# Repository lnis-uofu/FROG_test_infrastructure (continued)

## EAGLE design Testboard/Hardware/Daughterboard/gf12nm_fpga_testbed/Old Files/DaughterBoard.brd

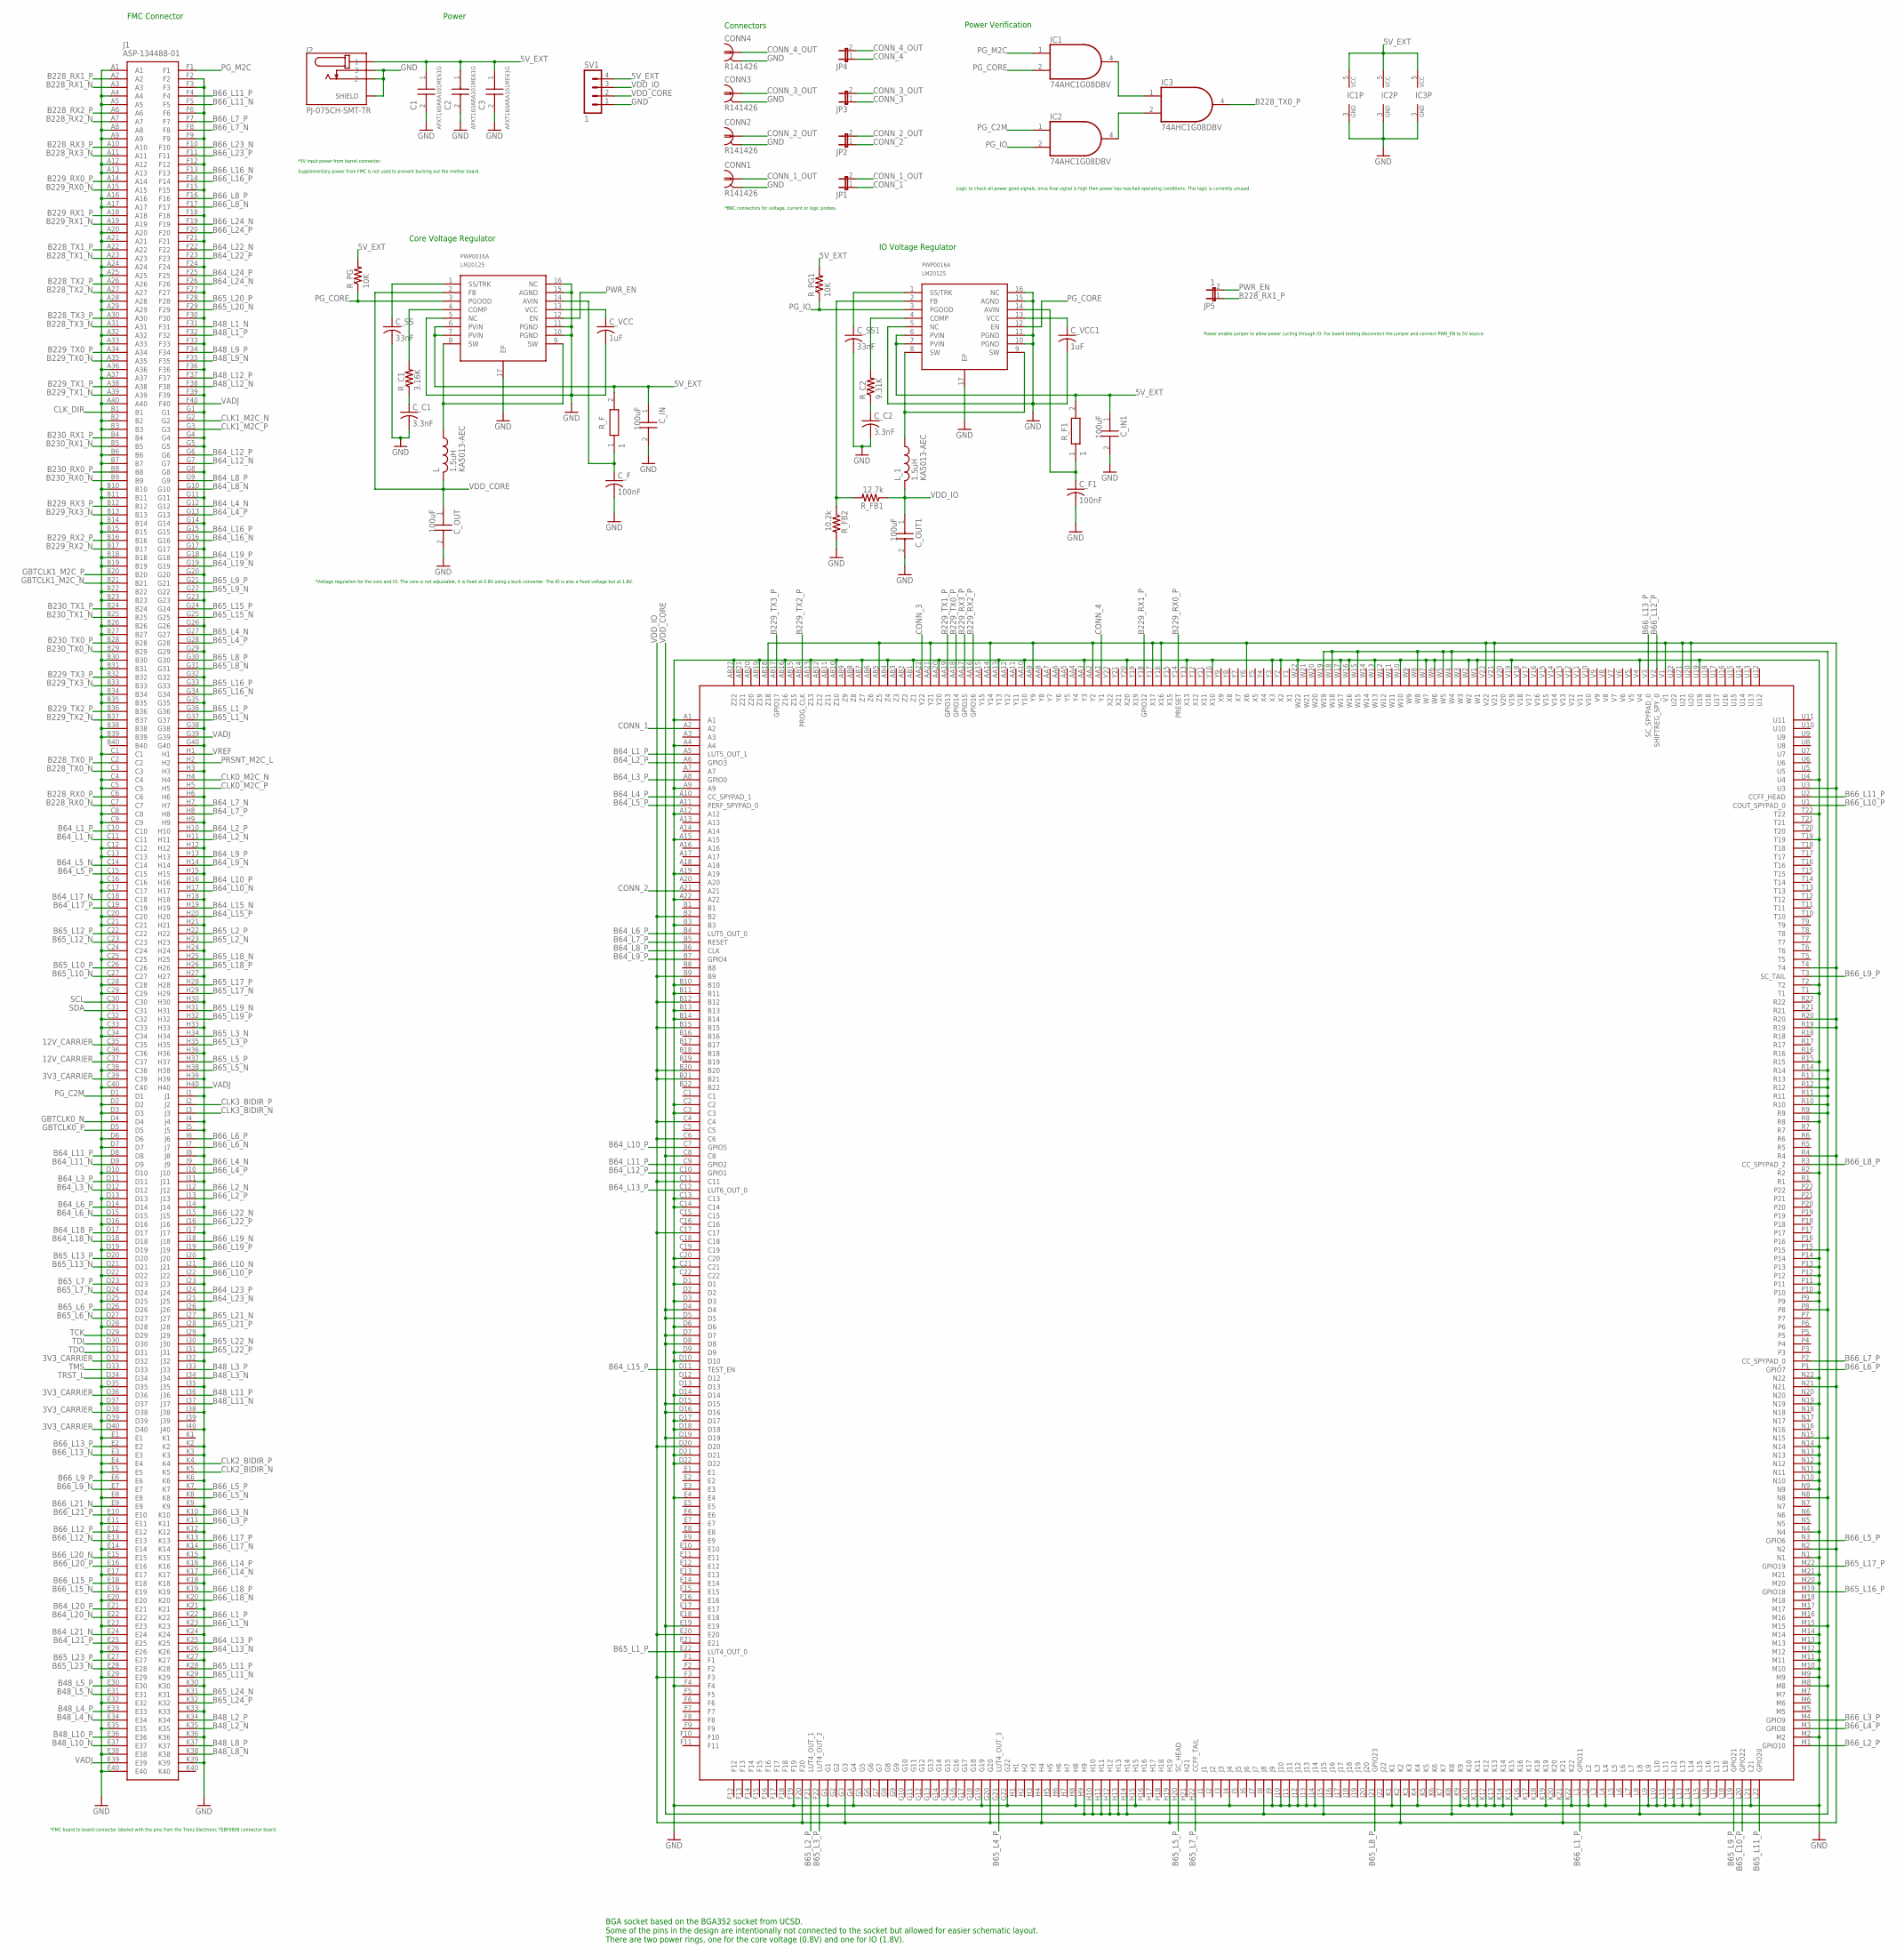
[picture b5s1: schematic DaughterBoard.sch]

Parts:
C1, C2, C3: APXT160ARA101ME61G; CAPAE530X610N
CONN1, CONN2, CONN3, CONN4: R141426
C_C1, C_C2: 3.3nF; C0805
C_F, C_F1: 100nF; C0805
C_IN, C_IN1: 100uF; CAPC2012X145N
C_OUT, C_OUT1: 100uF; CAPC2012X145N
C_SS, C_SS1: 33nF; C0805
C_VCC, C_VCC1: 1uF; C0805
IC1, IC2, IC3: 74AHC1G08DBV; SOT23-5
J1: ASP-134488-01; ASP13448801
J2: PJ-075CH-SMT-TR; CUI_PJ-075CH-SMT-TR
JP1, JP2, JP3, JP4: JP1E; JP1
JP5: 1; JP1
L: KA5013-AEC; INDDFN400X400X180-2N
L_1: KA5013-AEC; INDDFN400X400X180-2N
R_C1: 3.16K; R0805
R_C2: 9.31K; R0805
R_F, R_F1: 1; RESC1608X55N
R_FB1: 12.7k; R0805
R_FB2: 10.2k; R0805
R_PG, R_PG1: 10K; R0805
SV1: 1; MA04-1
U$1, U$3: LM20125/LM20125Q; SOP65P640X120-17T330L
U$2: BGA352; BGA484C100P22X22_2400X2400X220N

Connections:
3V3_CARRIER: J1.C39, J1.D32, J1.D36, J1.D38, J1.D40
5V_EXT: C1.1 (+), C2.1 (+), C3.1 (+), C_IN.1, C_IN1.1, IC1.5 (VCC), IC2.5 (VCC), IC3.5 (VCC), J2.1, R_F.2, R_F1.2, R_PG.2, R_PG1.2, SV1.4, U$1.6 (PVIN), U$1.7 (PVIN), U$3.6 (PVIN), U$3.7 (PVIN)
12V_CARRIER: J1.C35, J1.C37
B48_L1_N: J1.F31
B48_L1_P: J1.F32
B48_L2_N: J1.K35
B48_L2_P: J1.K34
B48_L3_N: J1.J34
B48_L3_P: J1.J33
B48_L4_N: J1.E34
B48_L4_P: J1.E33
B48_L5_N: J1.E31
B48_L5_P: J1.E30
B48_L8_N: J1.K38
B48_L8_P: J1.K37
B48_L9_N: J1.F35
B48_L9_P: J1.F34
B48_L10_N: J1.E37
B48_L10_P: J1.E36
B48_L11_N: J1.J37
B48_L11_P: J1.J36
B48_L12_N: J1.F38
B48_L12_P: J1.F37
B64_L1_N: J1.C11
B64_L1_P: J1.C10, U$2.A5 (LUT5_OUT_1)
B64_L2_N: J1.H11
B64_L2_P: J1.H10, U$2.A6 (GPIO3)
B64_L3_N: J1.D12
B64_L3_P: J1.D11, U$2.A8 (GPIO0)
B64_L4_N: J1.G12
B64_L4_P: J1.G13, U$2.A10 (CC_SPYPAD_1)
B64_L5_N: J1.C14
B64_L5_P: J1.C15, U$2.A11 (PERF_SPYPAD_0)
B64_L6_N: J1.D15
B64_L6_P: J1.D14, U$2.B4 (LUT5_OUT_0)
B64_L7_N: J1.H7
B64_L7_P: J1.H8, U$2.B5 (RESET)
B64_L8_N: J1.G10
B64_L8_P: J1.G9, U$2.B6 (CLK)
B64_L9_N: J1.H14
B64_L9_P: J1.H13, U$2.B7 (GPIO4)
B64_L10_N: J1.H17
B64_L10_P: J1.H16, U$2.C7 (GPIO5)
B64_L11_N: J1.D9
B64_L11_P: J1.D8, U$2.C9 (GPIO2)
B64_L12_N: J1.G7
B64_L12_P: J1.G6, U$2.C10 (GPIO1)
B64_L13_N: J1.K26
B64_L13_P: J1.K25, U$2.C12 (LUT6_OUT_0)
B64_L15_N: J1.H19
B64_L15_P: J1.H20, U$2.D11 (TEST_EN)
B64_L16_N: J1.G16
B64_L16_P: J1.G15
B64_L17_N: J1.C18
B64_L17_P: J1.C19
B64_L18_N: J1.D18
B64_L18_P: J1.D17
B64_L19_N: J1.G19
B64_L19_P: J1.G18
B64_L20_N: J1.E22
B64_L20_P: J1.E21
B64_L21_N: J1.E24
B64_L21_P: J1.E25
B64_L22_N: J1.F22
B64_L22_P: J1.F23
B64_L23_N: J1.J25
B64_L23_P: J1.J24
B64_L24_N: J1.F26
B64_L24_P: J1.F25
B65_L1_N: J1.G37
B65_L1_P: J1.G36, U$2.E22 (LUT4_OUT_0)
B65_L2_N: J1.H23
B65_L2_P: J1.H22, U$2.F21 (LUT4_OUT_1)
B65_L3_N: J1.H34
B65_L3_P: J1.H35, U$2.F22 (LUT4_OUT_2)
B65_L4_N: J1.G27
B65_L4_P: J1.G28, U$2.G21 (LUT4_OUT_3)
B65_L5_N: J1.H38
B65_L5_P: J1.H37, U$2.H20 (SC_HEAD)
B65_L6_N: J1.D27
B65_L6_P: J1.D26
B65_L7_N: J1.D24
B65_L7_P: J1.D23, U$2.H22 (CCFF_TAIL)
B65_L8_N: J1.G31
B65_L8_P: J1.G30, U$2.J21 (GPIO23)
B65_L9_N: J1.G22
B65_L9_P: J1.G21, U$2.L19 (GPIO21)
B65_L10_N: J1.C27
B65_L10_P: J1.C26, U$2.L20 (GPIO22)
B65_L11_N: J1.K29
B65_L11_P: J1.K28, U$2.L22 (GPIO20)
B65_L12_N: J1.C23
B65_L12_P: J1.C22
B65_L13_N: J1.D21
B65_L13_P: J1.D20
B65_L15_N: J1.G25
B65_L15_P: J1.G24
B65_L16_N: J1.G34
B65_L16_P: J1.G33, U$2.M19 (GPIO18)
B65_L17_N: J1.H29
B65_L17_P: J1.H28, U$2.M22 (GPIO19)
B65_L18_N: J1.H25
B65_L18_P: J1.H26
B65_L19_N: J1.H31
B65_L19_P: J1.H32
B65_L20_N: J1.F29
B65_L20_P: J1.F28
B65_L21_N: J1.J27
B65_L21_P: J1.J28
B65_L22_N: J1.J30
B65_L22_P: J1.J31
B65_L23_N: J1.E28
B65_L23_P: J1.E27
B65_L24_N: J1.K31
B65_L24_P: J1.K32
B66_L1_N: J1.K23
B66_L1_P: J1.K22, U$2.L1 (GPIO11)
B66_L2_N: J1.J12
B66_L2_P: J1.J13, U$2.M1 (GPIO10)
B66_L3_N: J1.K10
B66_L3_P: J1.K11, U$2.M4 (GPIO9)
B66_L4_N: J1.J9
B66_L4_P: J1.J10, U$2.M3 (GPIO8)
B66_L5_N: J1.K8
B66_L5_P: J1.K7, U$2.N3 (GPIO6)
B66_L6_N: J1.J7
B66_L6_P: J1.J6, U$2.P1 (GPIO7)
B66_L7_N: J1.F8
B66_L7_P: J1.F7, U$2.P2 (CC_SPYPAD_0)
B66_L8_N: J1.F17
B66_L8_P: J1.F16, U$2.R3 (CC_SPYPAD_2)
B66_L9_N: J1.E7
B66_L9_P: J1.E6, U$2.T3 (SC_TAIL)
B66_L10_N: J1.J21
B66_L10_P: J1.J22, U$2.U1 (COUT_SPYPAD_0)
B66_L11_N: J1.F5
B66_L11_P: J1.F4, U$2.U2 (CCFF_HEAD)
B66_L12_N: J1.E13
B66_L12_P: J1.E12, U$2.V2 (SHIFTREG_SPY_0)
B66_L13_N: J1.E3
B66_L13_P: J1.E2, U$2.V3 (SC_SPYPAD_0)
B66_L14_N: J1.K17
B66_L14_P: J1.K16
B66_L15_N: J1.E19
B66_L15_P: J1.E18
B66_L16_N: J1.F13
B66_L16_P: J1.F14
B66_L17_N: J1.K14
B66_L17_P: J1.K13
B66_L18_N: J1.K20
B66_L18_P: J1.K19
B66_L19_N: J1.J18
B66_L19_P: J1.J19
B66_L20_N: J1.E15
B66_L20_P: J1.E16
B66_L21_N: J1.E9
B66_L21_P: J1.E10
B66_L22_N: J1.J15
B66_L22_P: J1.J16
B66_L23_N: J1.F10
B66_L23_P: J1.F11
B66_L24_N: J1.F19
B66_L24_P: J1.F20
B228_RX0_N: J1.C7
B228_RX0_P: J1.C6
B228_RX1_N: J1.A3
B228_RX1_P: J1.A2, JP5.1
B228_RX2_N: J1.A7
B228_RX2_P: J1.A6
B228_RX3_N: J1.A11
B228_RX3_P: J1.A10
B228_TX0_N: J1.C3
B228_TX0_P: IC3.4 (O), J1.C2
B228_TX1_N: J1.A23
B228_TX1_P: J1.A22
B228_TX2_N: J1.A27
B228_TX2_P: J1.A26
B228_TX3_N: J1.A31
B228_TX3_P: J1.A30
B229_RX0_N: J1.A15
B229_RX0_P: J1.A14, U$2.Y14 (PRESET)
B229_RX1_N: J1.A19
B229_RX1_P: J1.A18, U$2.Y18 (GPIO12)
B229_RX2_N: J1.B17
B229_RX2_P: J1.B16, U$2.AA16 (GPIO16)
B229_RX3_N: J1.B13
B229_RX3_P: J1.B12, U$2.AA17 (GPIO15)
B229_TX0_N: J1.A35
B229_TX0_P: J1.A34, U$2.AA18 (GPIO14)
B229_TX1_N: J1.A39
B229_TX1_P: J1.A38, U$2.AA19 (GPIO13)
B229_TX2_N: J1.B37
B229_TX2_P: J1.B36, U$2.AB14 (PROG_CLK)
B229_TX3_N: J1.B33
B229_TX3_P: J1.B32, U$2.AB17 (GPIO17)
B230_RX0_N: J1.B9
B230_RX0_P: J1.B8
B230_RX1_N: J1.B5
B230_RX1_P: J1.B4
B230_TX0_N: J1.B29
B230_TX0_P: J1.B28
B230_TX1_N: J1.B25
B230_TX1_P: J1.B24
CLK0_M2C_N: J1.H4
CLK0_M2C_P: J1.H5
CLK1_M2C_N: J1.G2
CLK1_M2C_P: J1.G3
CLK2_BIDIR_N: J1.K5
CLK2_BIDIR_P: J1.K4
CLK3_BIDIR_N: J1.J3
CLK3_BIDIR_P: J1.J2
CLK_DIR: J1.B1
CONN_1: JP1.1, U$2.A2
CONN_1_OUT: CONN1.1, JP1.2
CONN_2: JP2.1, U$2.A21
CONN_2_OUT: CONN2.1, JP2.2
CONN_3: JP3.1, U$2.AA22 (Y22)
CONN_3_OUT: CONN3.1, JP3.2
CONN_4: JP4.1, U$2.AA1 (Y1)
CONN_4_OUT: CONN4.1, JP4.2
FB: R_FB1.2, R_FB2.1, U$3.2 (FB)
GBTCLK0_N: J1.D4
GBTCLK0_P: J1.D5
GBTCLK1_M2C_N: J1.B21
GBTCLK1_M2C_P: J1.B20
GND: C1.2 (-), C2.2 (-), C3.2 (-), CONN1.2, CONN1.3 (2), CONN1.4 (2), CONN1.5 (2), CONN2.2, CONN2.3 (2), CONN2.4 (2), CONN2.5 (2), CONN3.2, CONN3.3 (2), CONN3.4 (2), CONN3.5 (2), CONN4.2, CONN4.3 (2), CONN4.4 (2), CONN4.5 (2), C_C1.2, C_C2.2, C_F.2, C_F1.2, C_IN.2, C_IN1.2, C_OUT.2, C_OUT1.2, C_SS.2, C_SS1.2, C_VCC.2, C_VCC1.2, IC1.3 (GND), IC2.3 (GND), IC3.3 (GND), J1.A1, J1.A4, J1.A5, J1.A8, J1.A9, J1.A12, J1.A13, J1.A16, J1.A17, J1.A20, J1.A21, J1.A24, J1.A25, J1.A28, J1.A29, J1.A32, J1.A33, J1.A36, J1.A37, J1.A40, J1.B2, J1.B3, J1.B6, J1.B7, J1.B10, J1.B11, J1.B14, J1.B15, J1.B18, J1.B19, J1.B22, J1.B23, J1.B26, J1.B27, J1.B30, J1.B31, J1.B34, J1.B35, J1.B38, J1.B39, J1.C1, J1.C4, J1.C5, J1.C8, J1.C9, J1.C12, J1.C13, J1.C16, J1.C17, J1.C20, J1.C21, J1.C24, J1.C25, J1.C28, J1.C29, J1.C32, J1.C33, J1.C34, J1.C36, J1.C38, J1.C40, J1.D2, J1.D3, J1.D6, J1.D7, J1.D10, J1.D13, J1.D16, J1.D19, J1.D22, J1.D25, J1.D28, J1.D35, J1.D37, J1.D39, J1.E1, J1.E4, J1.E5, J1.E8, J1.E11, J1.E14, J1.E17, J1.E20, J1.E23, J1.E26, J1.E29, J1.E32, J1.E35, J1.E38, J1.E40, J1.F2, J1.F3, J1.F6, J1.F9, J1.F12, J1.F15, J1.F18, J1.F21, J1.F24, J1.F27, J1.F30, J1.F33, J1.F36, J1.F39, J1.G1, J1.G4, J1.G5, J1.G8, J1.G11, J1.G14, J1.G17, J1.G20, J1.G23, J1.G26, J1.G29, J1.G32, J1.G35, J1.G38, J1.G40, J1.H3, J1.H6, J1.H9, J1.H12, J1.H15, J1.H18, J1.H21, J1.H24, J1.H27, J1.H30, J1.H33, J1.H36, J1.H39, J1.J1, J1.J4, J1.J5, J1.J8, J1.J11, J1.J14, J1.J17, J1.J20, J1.J23, J1.J26, J1.J29, J1.J32, J1.J35, J1.J38, J1.J40, J1.K2, J1.K3, J1.K6, J1.K9, J1.K12, J1.K15, J1.K18, J1.K21, J1.K24, J1.K27, J1.K30, J1.K33, J1.K36, J1.K39, J2.2, J2.3, J2.4 (SHIELD), J2.5 (SHIELD), R_FB2.2, SV1.1, U$1.5 (NC), U$1.10 (PGND), U$1.11 (PGND), U$1.15 (AGND), U$1.16 (NC), U$1.17 (EP), U$2.A1, U$2.A4, U$2.A9, U$2.A12, U$2.A15, U$2.A19, U$2.A22, U$2.AA3 (Y3), U$2.AA10 (Y10), U$2.AA13 (Y13), U$2.AA20 (Y20), U$2.AB1 (Z1), U$2.AB4 (Z4), U$2.AB7 (Z7), U$2.AB10 (Z10), U$2.AB13 (Z13), U$2.AB16 (Z16), U$2.AB19 (Z19), U$2.AB22 (Z22), U$2.B3, U$2.B10, U$2.B11, U$2.B13, U$2.B14, U$2.C2, U$2.C3, U$2.C13, U$2.C14, U$2.C20, U$2.C21, U$2.D1, U$2.D3, U$2.D6, U$2.D9, U$2.D10, U$2.D14, U$2.D17, U$2.D18, U$2.D21, U$2.D22, U$2.E4, U$2.F4, U$2.F19, U$2.G1, U$2.G4, U$2.G19, U$2.G22, U$2.H8, U$2.H15, U$2.J4, U$2.J9, U$2.J10, U$2.J11, U$2.J12, U$2.J13, U$2.J14, U$2.K1, U$2.K4, U$2.K9, U$2.K10, U$2.K11, U$2.K12, U$2.K13, U$2.K14, U$2.K19, U$2.K22, U$2.L2, U$2.L4, U$2.L9, U$2.L10, U$2.L11, U$2.L12, U$2.L13, U$2.L14, U$2.L21, U$2.M2, U$2.M9, U$2.M10, U$2.M11, U$2.M12, U$2.M13, U$2.M14, U$2.M20, U$2.M21, U$2.N1, U$2.N4, U$2.N9, U$2.N10, U$2.N11, U$2.N12, U$2.N13, U$2.N14, U$2.N19, U$2.N22, U$2.P9, U$2.P10, U$2.P11, U$2.P12, U$2.P13, U$2.P14, U$2.R2, U$2.R8, U$2.R15, U$2.T1, U$2.T2, U$2.T19, U$2.T22, U$2.U4, U$2.U19, U$2.V4, U$2.V19, U$2.W1, U$2.W2, U$2.W6, U$2.W7, U$2.W10, U$2.W13, U$2.W16, U$2.W17, U$2.W22, U$2.Y2 (X2), U$2.Y3 (X3), U$2.Y10 (X10), U$2.Y13 (X13), U$2.Y20 (X20), U$3.5 (NC), U$3.10 (PGND), U$3.11 (PGND), U$3.15 (AGND), U$3.16 (NC), U$3.17 (EP)
unnamed: R_C2.2, U$3.4 (COMP)
unnamed: C_SS.1, U$1.1 (SS/TRK)
unnamed: R_C1.2, U$1.4 (COMP)
unnamed: C_C1.1, R_C1.1
unnamed: C_VCC.1, U$1.13 (VCC)
unnamed: C_C2.1, R_C2.1
unnamed: L.1, U$1.8 (SW), U$1.9 (SW)
unnamed: C_VCC1.1, U$3.13 (VCC)
unnamed: C_SS1.1, U$3.1 (SS/TRK)
unnamed: L_1.1, U$3.8 (SW), U$3.9 (SW)
unnamed: C_F1.1, R_F1.1, U$3.14 (AVIN)
unnamed: C_F.1, R_F.1, U$1.14 (AVIN)
unnamed: IC1.4 (O), IC3.1 (I0)
unnamed: IC2.4 (O), IC3.2 (I1)
PG_C2M: IC2.1 (I0), J1.D1
PG_CORE: IC1.2 (I1), R_PG.1, U$1.3 (PGOOD), U$3.12 (EN)
PG_IO: IC2.2 (I1), R_PG1.1, U$3.3 (PGOOD)
PG_M2C: IC1.1 (I0), J1.F1
PRSNT_M2C_L: J1.H2
PWR_EN: JP5.2, U$1.12 (EN)
SCL: J1.C30
SDA: J1.C31
TCK: J1.D29
TDI: J1.D30
TDO: J1.D31
TMS: J1.D33
TRST_L: J1.D34
VADJ: J1.E39, J1.F40, J1.G39, J1.H40
VDD_CORE: C_OUT.1, L.2, SV1.2, U$1.2 (FB), U$2.C8, U$2.D4, U$2.D5, U$2.D7, U$2.D8, U$2.D15, U$2.D16, U$2.D19, U$2.E19, U$2.H9, U$2.H10, U$2.H11, U$2.H12, U$2.H13, U$2.H14, U$2.J8, U$2.J15, U$2.K8, U$2.K15, U$2.L8, U$2.L15, U$2.M8, U$2.M15, U$2.N8, U$2.N15, U$2.P8, U$2.P15, U$2.R9, U$2.R10, U$2.R11, U$2.R12, U$2.R13, U$2.R14, U$2.W4, U$2.W5, U$2.W8, U$2.W15, U$2.W18, U$2.W19
VDD_IO: C_OUT1.1, L_1.2, R_FB1.1, SV1.3, U$2.AA2 (Y2), U$2.AA9 (Y9), U$2.AA14 (Y14), U$2.AA21 (Y21), U$2.AB5 (Z5), U$2.AB18 (Z18), U$2.B2, U$2.B9, U$2.B12, U$2.B15, U$2.B20, U$2.B21, U$2.C4, U$2.C6, U$2.C11, U$2.C17, U$2.D20, U$2.E20, U$2.F3, U$2.F20, U$2.G3, U$2.G20, U$2.H4, U$2.H19, U$2.K2, U$2.K21, U$2.N2, U$2.N21, U$2.R4, U$2.R19, U$2.R20, U$2.T4, U$2.U3, U$2.U20, U$2.U21, U$2.V1, U$2.V21, U$2.V22, U$2.Y6 (X6), U$2.Y16 (X16), U$2.Y17 (X17)
VREF: J1.H1

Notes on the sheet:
Power
Connectors
FMC Connector
Core Voltage Regulator
*Voltage regulation for the core and IO. The core is not adjustable, it is fixed at 0.8V using a buck converter. The IO is also a fixed voltage but at 1.8V.
*BNC connectors for voltage, current or logic probes.
*5V input power from barrel connector. Supplementary power from FMC is not used to prevent burning out the mother board.
*FMC board to board connector labeled with the pins from the Trenz Electronic TEBF0808 connector board.
IO Voltage Regulator
Power Verification
Logic to check all power good signals, once final signal is high then power has reached operating conditions. This logic is currently unused.
BGA socket based on the BGA352 socket from UCSD. Some of the pins in the design are intentionally not connected to the socket but allowed for easier schematic layout. There are two power rings, one for the core voltage (0.8V) and one for IO (1.8V).
Power enable jumper to allow power cycling through IO. For board testing disconnect the jumper and connect PWR_EN to 5V source.

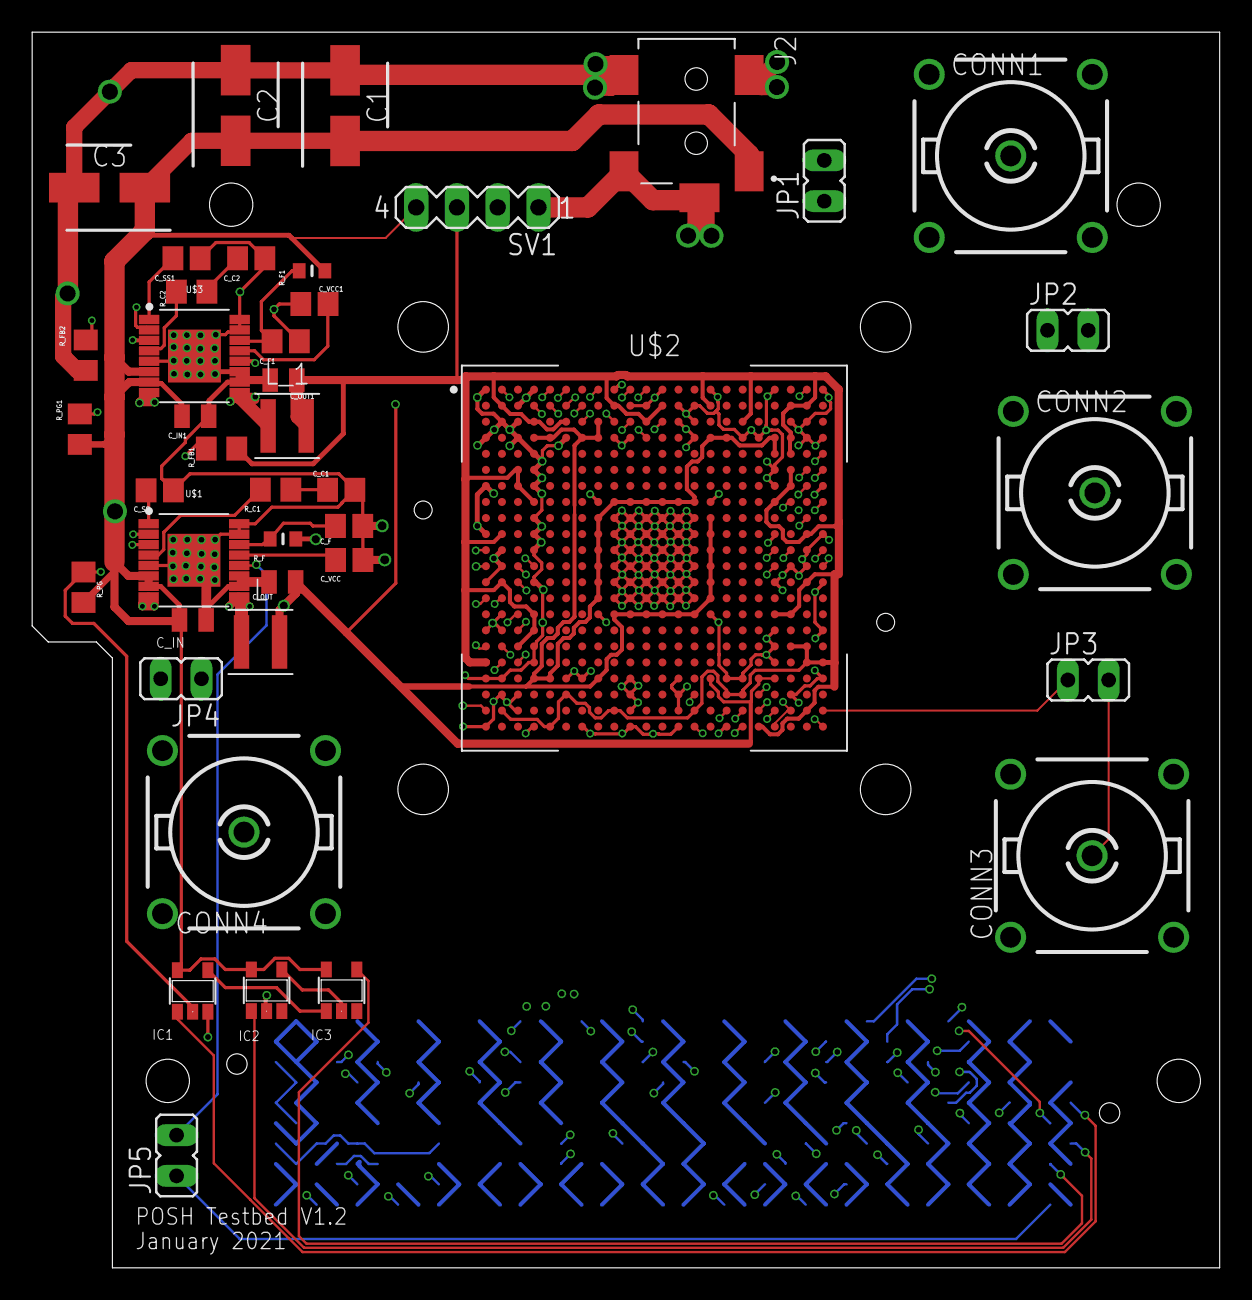
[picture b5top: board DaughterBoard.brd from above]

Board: 4 copper layers, 74.0 x 77.0 mm, 43 parts (1 on the bottom side), 84 nets.

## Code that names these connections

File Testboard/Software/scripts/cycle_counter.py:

output_string = ""

with open("io_ring_bitstream.bit", "w") as bitstream_file:

    # First 10 i/o
    output_string = "1\n"*12 + output_string

    
    # sb_6_6
    output_string = "0\n"*220 + output_string
    
    # cbx_6_6
    output_string = "0\n"*18 + output_string

    # GPIO18
    output_string = "1" + "\n" + output_string
    

    # sb_5_6
    output_string = "0\n"*358 + output_string
    
    # cbx_5_6
    output_string = "0\n"*18 + output_string

    # GPIO19
    output_string = "1" + "\n" + output_string
    
    
    # sb_4_6
    output_string = "0\n"*358 + output_string
    
    # cbx_4_6
    output_string = "0\n"*18 + output_string

    # GPIO20
    output_string = "1" + "\n" + output_string
    
    
    # sb_3_6
    output_string = "0\n"*358 + output_string
    
    # cbx_3_6
    output_string = "0\n"*18 + output_string

    # GPIO21
    output_string = "1" + "\n" + output_string
    
    
    # sb_2_6
    output_string = "0\n"*358 + output_string
    
    # cbx_2_6
    output_string = "0\n"*18 + output_string

    # GPIO22
    output_string = "1" + "\n" + output_string
    

    # sb_1_6
    output_string = "0\n"*358 + output_string
    
    # cbx_1_6
    output_string = "0\n"*18 + output_string

    # GPIO23
    output_string = "1" + "\n" + output_string
    

    # sb_0_6
    output_string = "0\n"*40 + output_string
    
    # sb_0_5
    output_string = "0\n"*379 + output_string
    
    # cby_0_6
    output_string = "0\n"*6 + output_string
    
    # GPIO0
    output_string = "1" + "\n" + output_string
    

    # sb_0_4
    output_string = "0\n"*379 + output_string
    
    # cby_0_5
    output_string = "0\n"*6 + output_string

    # GPIO1
    output_string = "1" + "\n" + output_string
    

    # sb_0_3
    output_string = "0\n"*379 + output_string
    
    # cby_0_4
    output_string = "0\n"*6 + output_string

    # GPIO2
    output_string = "1" + "\n" + output_string
    

    # sb_0_2
    output_string = "0\n"*379 + output_string
    
    # cby_0_3
    output_string = "0\n"*6 + output_string

    # GPIO3
    output_string = "1" + "\n" + output_string
    

    # sb_0_1
    output_string = "0\n"*379 + output_string
    
    # cby_0_2
    output_string = "0\n"*6 + output_string

    # GPIO4
    output_string = "1" + "\n" + output_string


    # # 1110111 pattern
    # output_string = "1\n"*3 + "1\n" + "1\n"*3 + output_string
    # output_string = "0\n"*10 + output_string # padding

    # # 0001000 pattern
    # output_string = "0\n"*3 + "1\n" + "0\n"*3 + output_string
    # output_string = "0\n"*10 + output_string # padding

    # # 11001100 pattern
    # output_string = "1\n"*2 + "0\n"*2 + "1\n"*2 + "0\n"*2 + output_string
    # output_string = "0\n"*10 + output_string # padding

    # sb_0_0
    output_string = "0\n"*220 + output_string
    
    # cby_0_1
    output_string = "0\n"*6 + output_string

    # GPIO5
    output_string = "1" + "\n" + output_string
    

    # sb_1_0
    output_string = "0\n"*402 + output_string
    
    # cbx_1_0
    output_string = "0\n"*126 + output_string
    
    # cby_1_1
    output_string = "0\n"*120 + output_string

    # grid_clb_1_1_
    output_string = "0\n"*1115 + output_string


    bitstream_file.write(output_string)

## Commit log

2022-02-09 Add packaging / demoboard / testboard related files.
2022-02-10 Testboard hw cleanup
2022-02-10 Add vivado to development tools.
2022-02-10 typo/rephrase
2022-02-10 Cleanup packaging directory
2022-02-10 Add BGA package sources
2022-02-10 typo in name
2022-02-10 Update ChipOnBoard and add assembly drawing
2022-02-10 Add Package design source as a submodule
2022-02-10 Clean packaging repo
